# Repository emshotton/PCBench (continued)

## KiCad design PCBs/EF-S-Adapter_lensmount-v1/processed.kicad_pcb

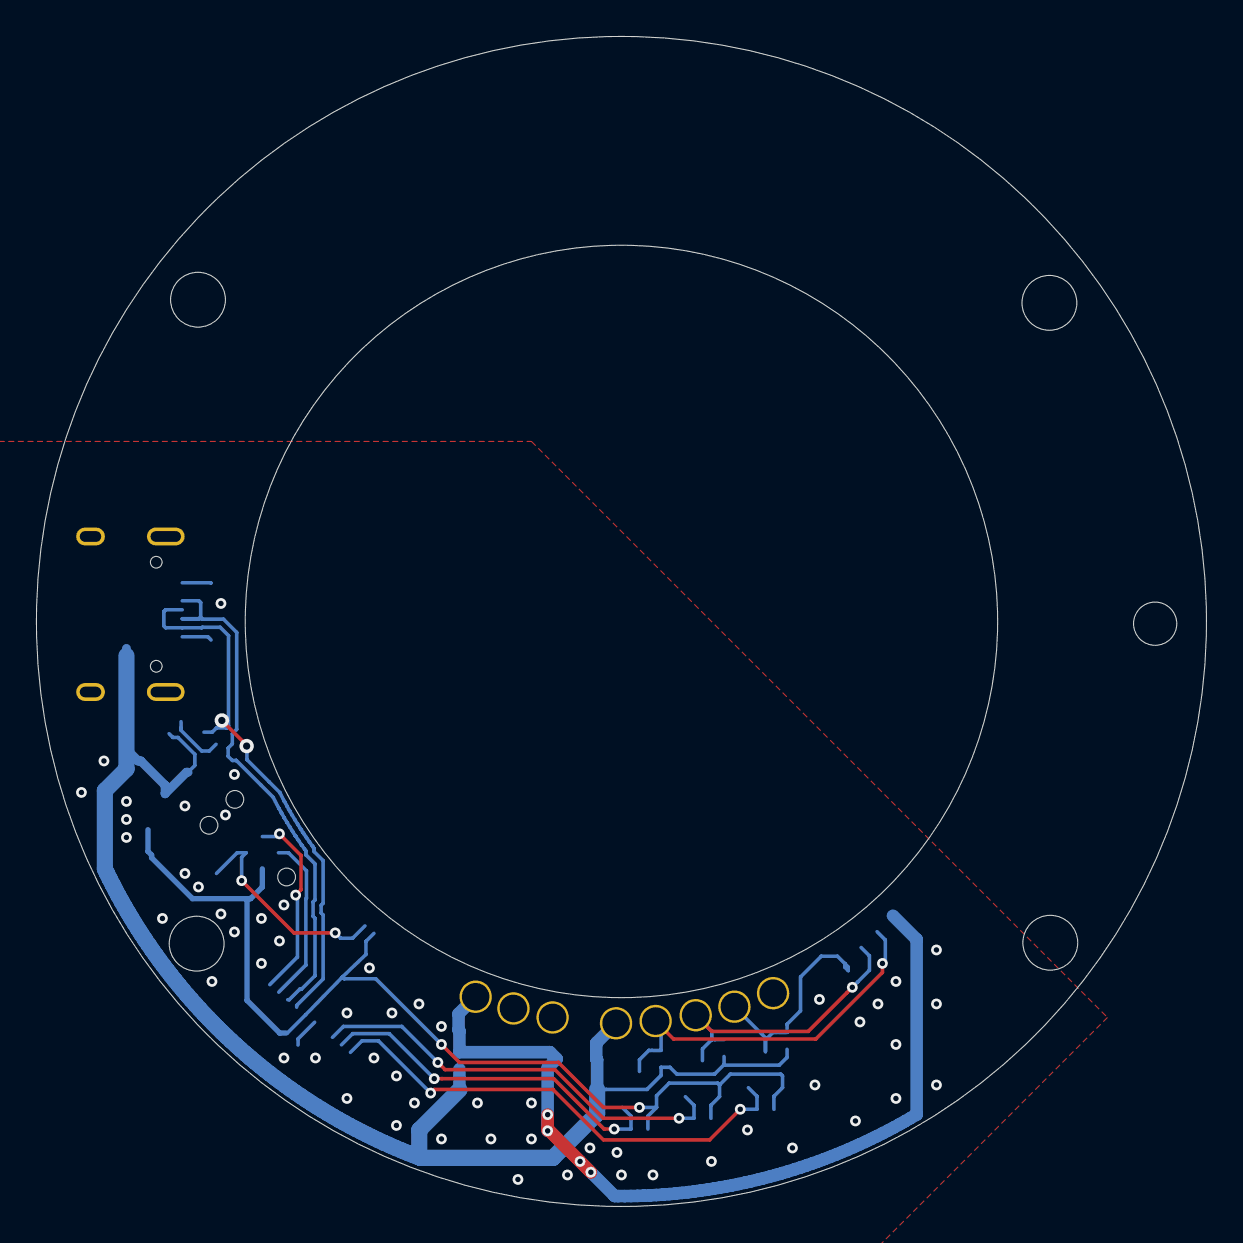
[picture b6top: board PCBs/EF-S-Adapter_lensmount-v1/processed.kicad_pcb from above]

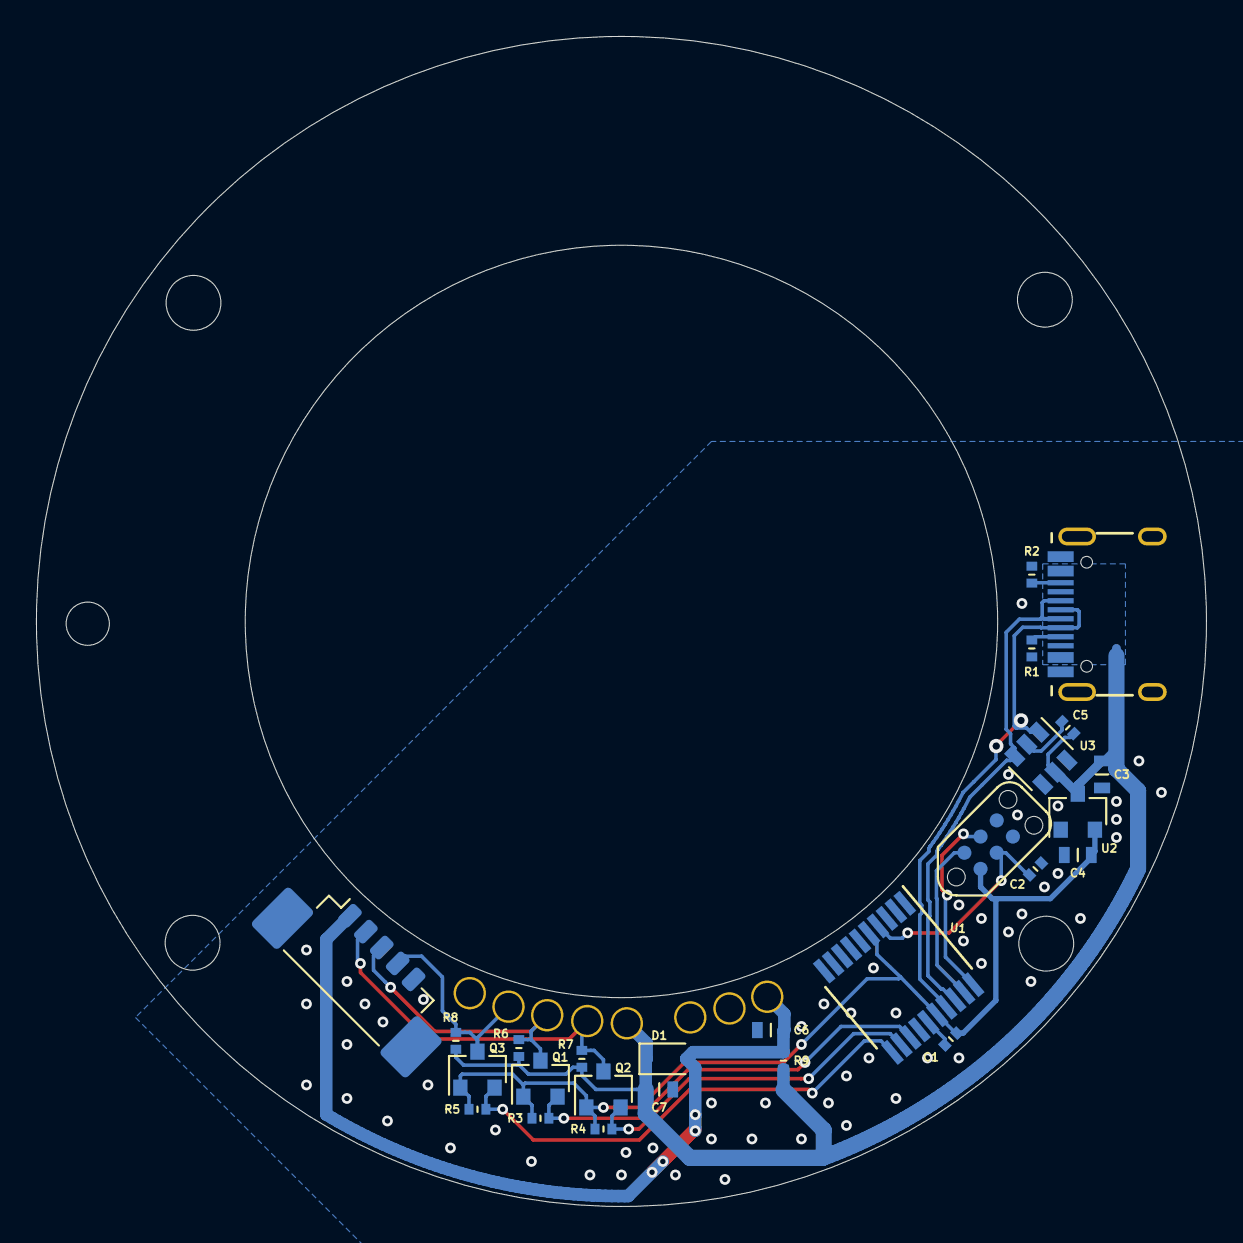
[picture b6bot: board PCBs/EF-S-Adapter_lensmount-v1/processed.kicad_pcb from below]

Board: 2 copper layers, 65.0 x 65.0 mm, 34 parts (26 on the bottom side), 17 nets.

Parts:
C1, C2, C5: 100n; C_0402
C3, C4, C6, C7: 1u; C_0603
D1: DNP; D_SOD-323F
J1: VBAT; PH-MVF-5365
J2, J3: AGND; PH-MVF-5365
J4: VDD; PH-MVF-5365
J5: DOUT; PH-MVF-5365
J6: DIN; PH-MVF-5365
J7: DCLK; PH-MVF-5365
J8: DGND; PH-MVF-5365
J9: USB; USB-C 16Pin
J10: Picoblade DNP; Molex_PicoBlade_53398-0571_1x05-1MP_P1.25mm_Vertical
P1: TC2030-CTX-Tag-Connect; TC2030
Q1, Q2, Q3: 2N7002; SOT-23
R1, R2, R3, R4, R5, R6, R7, R8, R9: 5k1; R_0402
U1: STM32F042F6Px; TSSOP-20_4.4x6.5mm_P0.65mm
U2: XC6206PxxxMR; SOT-23
U3: USBLC6-4; SOT-23-6

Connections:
+3V3: C1.1, C4.1, P1.1, Q1.1, Q2.1, Q3.1, R3.1, R4.1, R5.1, U1.5, U1.16, U2.2
+BATT: C6.1, D1.2, J1.1, J10.1, R9.1
D+: J9.A6, J9.B6, U1.18, U3.3
D-: J9.A7, J9.B7, U1.17, U3.1
DCLK_3V3: Q3.2, R5.2, U1.11
DCLK_5V: J7.1, J10.4, Q3.3, R8.2
DIN_3V3: Q1.2, R3.2, U1.13
DIN_5V: J6.1, J10.3, Q1.3, R6.2
DOUT_3V3: Q2.2, R4.2, U1.12
DOUT_5V: J5.1, J10.2, Q2.3, R7.2
GND: C1.2, C2.2, C3.2, C4.2, C5.2, C6.2, C7.2, J2.1, J3.1, J8.1, J9.A1, J9.A12, J9.B1, J9.B12, J9.S1, J10.5, J10.MP, P1.5, R1.1, R2.1, U1.15, U2.1, U3.2
NRST: C2.1, P1.3, U1.4
unnamed: J9.A5, R1.2
unnamed: J9.B5, R2.2
SWCLK: P1.4, U1.20
SWDIO: P1.2, U1.19
VBUS: C3.1, C5.1, C7.1, D1.1, J4.1, J9.A4, J9.A9, J9.B4, J9.B9, R6.1, R7.1, R8.1, R9.2, U2.3, U3.5

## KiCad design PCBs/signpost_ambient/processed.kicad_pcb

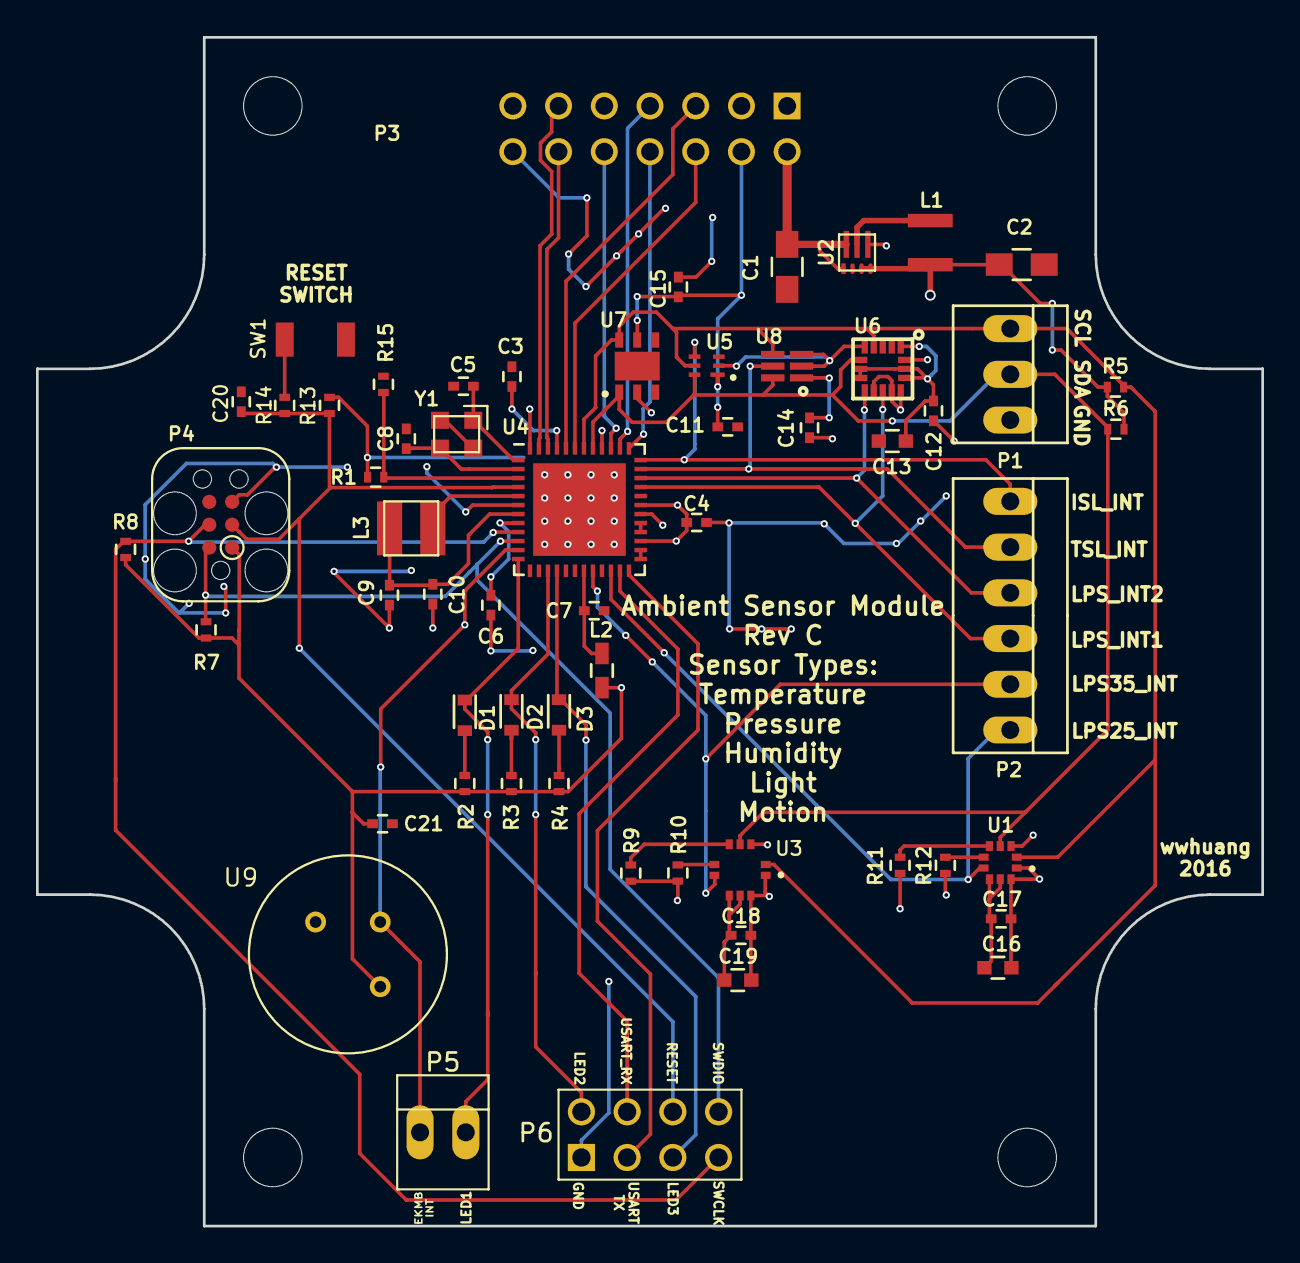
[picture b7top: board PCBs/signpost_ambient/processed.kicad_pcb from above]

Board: 4 copper layers, 68.1 x 66.0 mm, 63 parts (0 on the bottom side), 44 nets.

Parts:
C1, C2: GENERIC_C_0805; C_0805_HandSoldering
C3, C4, C6, C7, C10, C11, C12, C14, C15, C17, C18, C21: C_0.1u_0402_10V_10%_JB; C_0402
C5, C8, C20: GENERIC_C_0402; C_0402
C9: C_4.7u_0402_10V_10%_X5R; C_0402
C13, C16, C19: C_10u_0603_10V_10%_JB; C_0603
D1, D2, D3: LED; D_0603
H1, H2, H3, H4: SIGNPOST_HOLE
L1: .47 uH; DFE322512C
L2: 1.5k Ohm; C_0603_HandSoldering
L3: 22uH; 1212
P1: CONN_01X03; PINHEAD1-3
P2: CONN_01X06; PINHEAD1-6
P3: SIGNPOST_MODULE_GENERIC
P4: JLINK-TC; TC2030-IDC
P5: CONN_01X02; PINHEAD1-2
P6: CONN_02X04; PINHEAD2-4
R1, R5, R6: R_10k_0402_1%,100ppm/c,0.063W; R_0402
R2, R3, R4: R_1K_0402_1%,100ppm/c,0.2W; R_0402
R7, R8, R9, R10, R11, R12, R13: R_100K_0402_0.5%,25ppm/c,0.063W; R_0402
R14: GENERIC_R_0402; R_0402
R15: R_0_0402_.1W; R_0402
SW1: BSU-1000P; B3U-1000p
U1: LPS25HB; HLGA-10L_2.5x2.5mm
U2: TPS62086; RLT0007A
U3: LPS35HW; CCLGA-10L_3.5x3.5mm
U4: SAM4LC8A; QFN-48-1EP_7x7mm_Pitch0.5mm
U5: ISL29035; L6_1.5x1.6mm
U6: LPS331AP; HCLGA-16L
U7: Si7021; DFN_3x3mm_1mm
U8: TSL2561; DFN2
U9: EKMB1101111
Y1: FH1600015; FHXXX

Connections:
+3V3: C2.1, C3.1, C4.1, C6.1, C11.1, C12.1, C13.1, C14.1, C15.1, C16.1, C17.1, C18.1, C19.1, C21.1, L1.1, L2.2, P3.4, P4.1, R1.1, R2.2, R3.2, R4.2, R5.1, R6.1, R7.2, R8.1, R9.1, R10.1, R12.1, R13.1, U1.1, U1.10, U2.3, U2.4, U3.1, U3.10, U4.8, U4.27, U4.31, U4.40, U4.45, U5.1, U6.1, U6.7, U6.8, U6.14, U6.15, U7.5, U8.1, U9.2
+5V: C1.1, P3.2, U2.1, U2.7
/CNTR_PPS: P3.7, U4.38
/CNTR_SCL: P3.5, U4.44
/CNTR_SDA: P3.6, U4.43
/EKMB_INT: P5.1, U4.11, U9.1
/ISL_INT: P2.1, U4.36, U5.4
/LED_1: D1.1, P5.2, U4.12
/LED_2: D2.1, P6.2, U4.15
/LED_3: D3.1, P6.5, U4.16
/LPS25_INT: P2.6, U1.7, U4.22
/LPS35_INT: P2.5, U3.7, U4.20
/LPS_INT1: P2.4, U4.33, U6.11
/LPS_INT2: P2.3, U4.34, U6.9
/MOD_IN: P3.10, U4.39
/MOD_OUT: P3.8, U4.37
/SAM4L_RESET: C20.1, P4.3, P6.6, R13.2, R14.1, U4.4
/SAM4L_SWDCLK: P4.4, P6.7, R8.2, U4.9
/SAM4L_SWDIO: P4.2, P6.8, R7.1, U4.10
/TSL_INT: P2.2, U4.35, U8.5
/USART_RX: P6.4, U4.23
/USART_TX: P6.3, U4.24
/USB_D+: P3.11, U4.47
/USB_D-: P3.12, U4.46
/VDDANA: C7.1, L2.1, U4.19
/VDD_CORE: L3.1, U4.5
/VDD_OUT: C9.1, C10.1, L3.2, U4.7
/sensors/LPS25_CS: R12.2, U1.6
/sensors/LPS25_SA0: R11.2, U1.5
/sensors/LPS35_CS: R10.2, U3.6
/sensors/LPS35_SA0: R9.2, U3.5
/xin: C5.1, U4.1, Y1.1
/xout: C8.1, U4.2, Y1.3
GND: C1.2, C2.2, C3.2, C4.2, C5.2, C6.2, C7.2, C8.2, C9.2, C10.2, C11.2, C12.2, C13.2, C14.2, C15.2, C16.2, C17.2, C18.2, C19.2, C20.2, C21.2, P1.3, P3.1, P3.14, P4.5, P6.1, R11.1, R15.2, SW1.2, U1.3, U1.8, U1.9, U2.5, U3.3, U3.8, U3.9, U4.6, U4.17, U4.30, U4.48, U4.49, U5.2, U6.5, U6.10, U6.12, U6.13, U6.16, U7.2, U8.2, U8.3, U9.3, Y1.2, Y1.4
unnamed: D1.2, R2.1
unnamed: D2.2, R3.1
unnamed: D3.2, R4.1
unnamed: L1.2, U2.6
unnamed: R1.2, R15.1, U4.3
unnamed: R14.2, SW1.1
unnamed: U4.25, U4.26
unnamed: U4.28, U4.29
SCL: P1.1, R5.2, U1.2, U3.2, U4.42, U5.5, U6.4, U7.6, U8.4
SDA: P1.2, R6.2, U1.4, U3.4, U4.41, U5.6, U6.6, U7.1, U8.6

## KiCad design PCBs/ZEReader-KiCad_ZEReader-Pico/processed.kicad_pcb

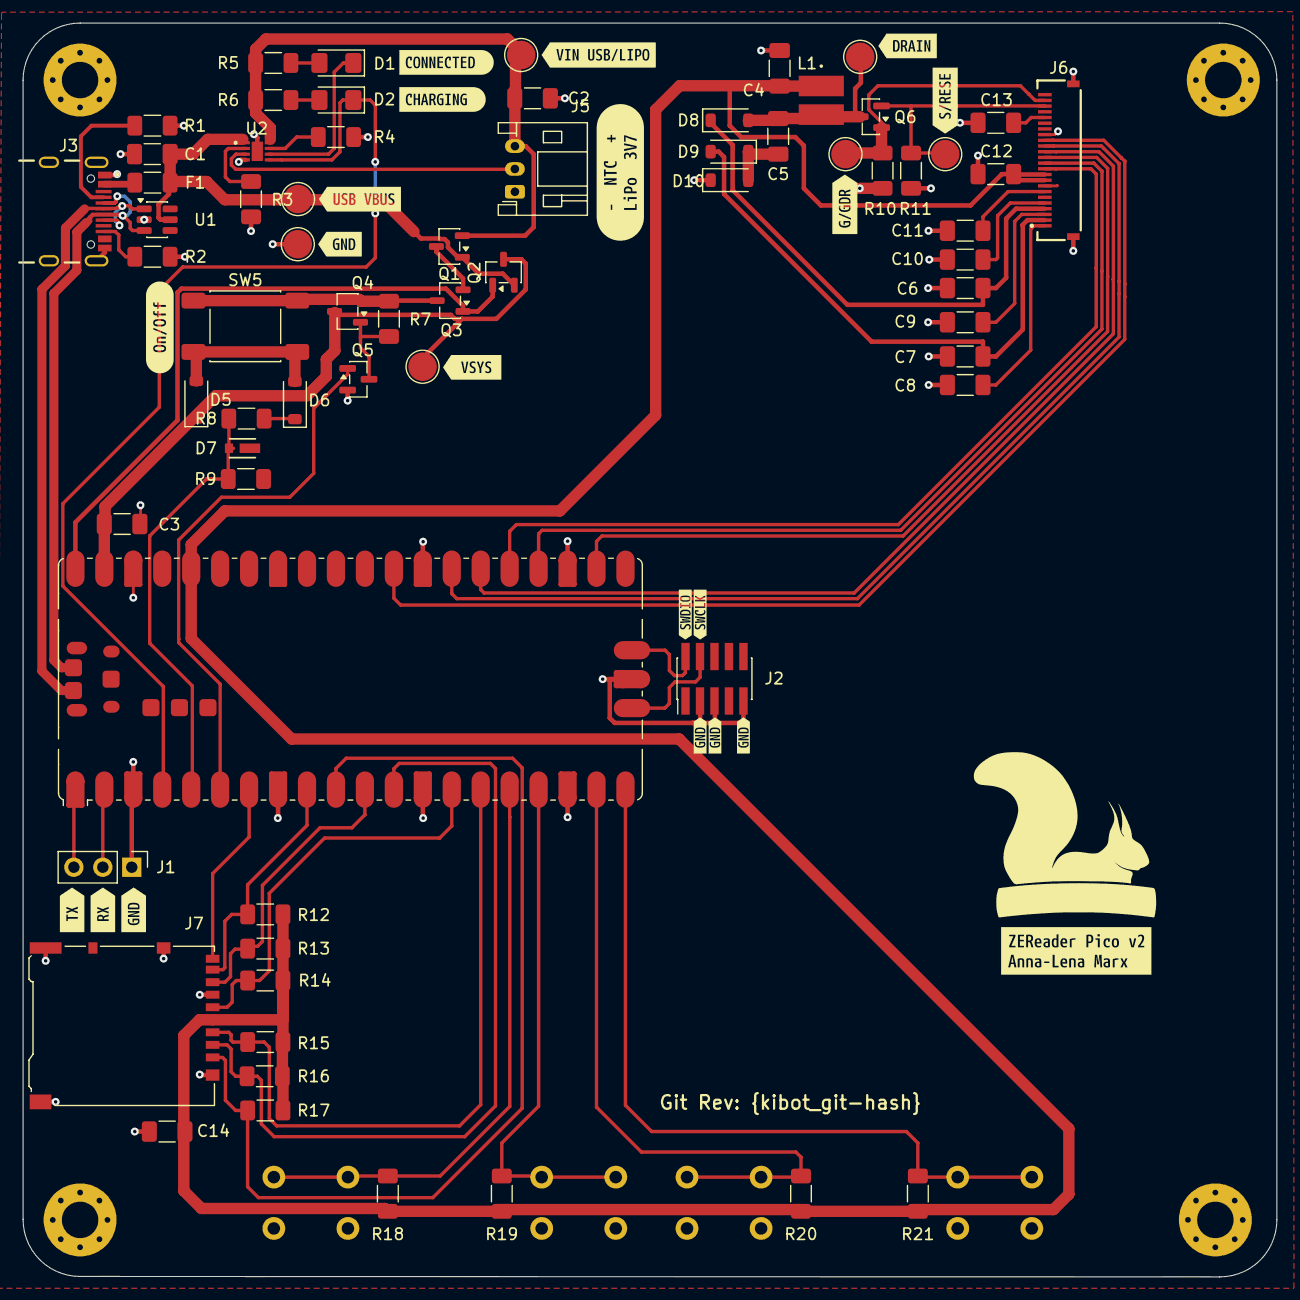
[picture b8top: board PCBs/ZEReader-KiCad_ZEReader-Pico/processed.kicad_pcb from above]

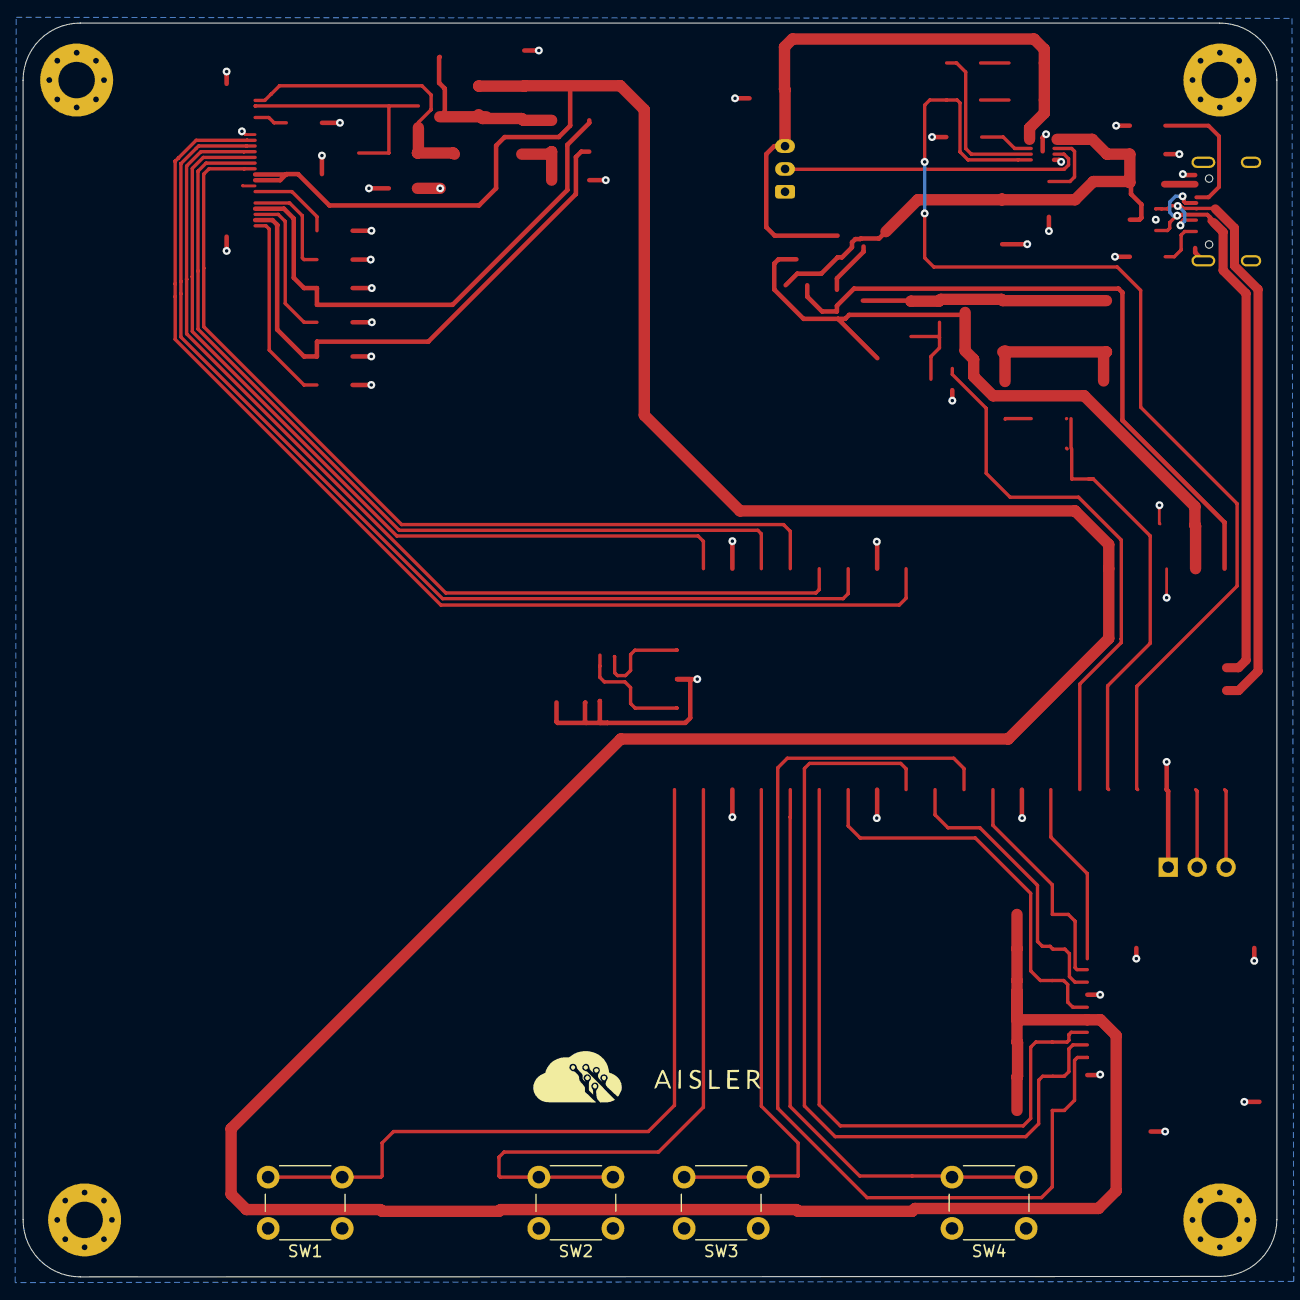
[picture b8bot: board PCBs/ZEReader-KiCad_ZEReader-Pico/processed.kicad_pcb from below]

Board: 2 copper layers, 110.0 x 110.0 mm, 96 parts (4 on the bottom side), 57 nets.

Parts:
A1: RaspberryPi_Pico; RaspberryPi_Pico_SMD
C1, C2, C3, C14: 10uF; C_1206_3216Metric_Pad1.33x1.80mm_HandSolder
C4, C5: 4.7uF; C_1206_3216Metric_Pad1.33x1.80mm_HandSolder
C6, C7, C9, C10, C13: 1uF, 25V; C_1206_3216Metric_Pad1.33x1.80mm_HandSolder
C8: 1uF, 50V; C_1206_3216Metric_Pad1.33x1.80mm_HandSolder
C11: 1uF, 10V; C_1206_3216Metric_Pad1.33x1.80mm_HandSolder
C12: 10uF, 10V; C_1206_3216Metric_Pad1.33x1.80mm_HandSolder
D1, D2: LED; LED_1206_3216Metric_Pad1.42x1.75mm_HandSolder
D5, D6, D8, D9, D10: MBR0530; D_SOD-123
D7: Zener 3V3; DIO_TDZVT_ROM
DRAIN1: BSS138_Drain; TestPoint_Pad_D2.5mm
F1: Polyfuse; R_1206_3216Metric_Pad1.30x1.75mm_HandSolder
G/GDR1: BSS138_Gate; TestPoint_Pad_D2.5mm
H1, H2, H3, H4: MountingHole_Pad; MountingHole_3.2mm_M3_Pad_Via
J1: UART; PinHeader_1x03_P2.54mm_Vertical
J2: Conn_02x05_Odd_Even; PinHeader_2x05_P1.27mm_Vertical_SMD
J3: USB4105-GF-A; GCT_USB4105-GF-A
J5: Conn_01x03_Socket; JST_PH_S3B-PH-K_1x03_P2.00mm_Horizontal
J6: FFC2B28-24-G; GCT_FFC2B28-24-G
J7: Micro_SD_Card_Det2; microSD_HC_Hirose_DM3AT-SF-PEJM5
L1: 10uH; IND_IFSC_1515AH_VIS-L
Q1, Q2, Q3, Q4: DMG2305UX-7; SOT-23-3
Q5, Q6: BSS138; SOT-23
R1, R2: 5.1k; R_1206_3216Metric_Pad1.30x1.75mm_HandSolder
R3: 604, 1%; R_1206_3216Metric_Pad1.30x1.75mm_HandSolder
R4: 27k, 1%; R_1206_3216Metric_Pad1.30x1.75mm_HandSolder
R5, R6, R7, R9, R10, R12, R13, R14, R15, R16, R17, R18, R19, R20, R21: 10k; R_1206_3216Metric_Pad1.30x1.75mm_HandSolder
R8: 1k; R_1206_3216Metric_Pad1.30x1.75mm_HandSolder
R11: 0.47; R_1206_3216Metric_Pad1.30x1.75mm_HandSolder
S/RESE1: BSS138_Source; TestPoint_Pad_D2.5mm
SW1, SW2, SW3, SW4: SW_Push; SW_PUSH_6mm
SW5: SW_Push; SW_Push_1P1T_NO_E-Switch_TL3301NxxxxxG
TP1: USB_VBUS; TestPoint_Pad_D2.5mm
TP2: V_USB_LIPO; TestPoint_Pad_D2.5mm
TP3: VSYS; TestPoint_Pad_D2.5mm
TP_GND1: TestPoint_Pad_D2.5mm
U1: USBLC6-2SC6; SOT-23-6
U2: BQ25170JDSGR; WSON8_BQ2517_TEX
kibuzzard-1: G***; kibuzzard-6910EAB5
kibuzzard-2: G***; kibuzzard-6910F1E0
kibuzzard-3: G***; kibuzzard-6910EA92
kibuzzard-4: G***; kibuzzard-6910F073
kibuzzard-5: G***; kibuzzard-6910F03B
kibuzzard-6: G***; kibuzzard-6910EACE
kibuzzard-7: G***; kibuzzard-6910EA89
kibuzzard-8: G***; kibuzzard-6910EAAC
kibuzzard-10: G***; kibuzzard-6910EB09
kibuzzard-14: G***; kibuzzard-6910EC15
kibuzzard-15: G***; kibuzzard-6910EC3B
kibuzzard-16: G***; kibuzzard-6910EC48
kibuzzard-17: G***; kibuzzard-6910ECBF
kibuzzard-691E57BD: G***; kibuzzard-691E57BD
kibuzzard-691E5833: G***; kibuzzard-691E5833
kibuzzard-691EE38D: G***; kibuzzard-691EE38D
kibuzzard-691EE385: G***; kibuzzard-691EE385
kibuzzard-691EE480: G***; kibuzzard-691EE480
kibuzzard-691EE489: G***; kibuzzard-691EE489
kibuzzard-691EE495: G***; kibuzzard-691EE495

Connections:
+3.3V: A1.36 (3V3), C4.1, C12.2, C14.1, J6.9, J6.10, J7.4 (VDD), L1.1, R12.1, R13.1, R14.1, R15.1, R16.1, R17.1, R18.2, R19.2, R20.1, R21.1
/01_MCU/BTN_1: A1.20 (GPIO15), R21.2, SW1.2
/01_MCU/BTN_2: A1.19 (GPIO14), R20.2, SW2.2
/01_MCU/BTN_3: A1.17 (GPIO13), R19.1, SW3.2
/01_MCU/BTN_4: A1.16 (GPIO12), R18.1, SW4.2
/01_MCU/CHARGING: A1.4 (GPIO2), D2.1 (K), U2.5 (STAT)
/01_MCU/EPD_BUSY: A1.29 (GPIO22), J6.16
/01_MCU/EPD_CS: A1.22 (GPIO17), J6.13
/01_MCU/EPD_DC: A1.26 (GPIO20), J6.14
/01_MCU/EPD_DIN: A1.25 (GPIO19), J6.11
/01_MCU/EPD_RST: A1.27 (GPIO21), J6.15
/01_MCU/EPD_SCK: A1.24 (GPIO18), J6.12
/01_MCU/SD_CLK-SCLK: A1.14 (GPIO10), J7.5 (CLK), R14.2
/01_MCU/SD_CMD-DI: A1.15 (GPIO11), J7.3 (CMD), R15.2
/01_MCU/SD_DAT0-DO: A1.11 (GPIO8), J7.7 (DAT0), R13.2
/01_MCU/SD_DAT1: A1.9 (GPIO6), J7.8 (DAT1), R12.2
/01_MCU/SD_DAT2: A1.10 (GPIO7), J7.1 (DAT2), R17.2
/01_MCU/SD_DAT3-CD-CS: A1.12 (GPIO9), J7.2 (DAT3/CD), R16.2
/01_MCU/SD_DET_B: A1.7 (GPIO5), J7.9 (DET_B)
/01_MCU/UC_OFF: A1.6 (GPIO4), Q5.1 (G)
/01_MCU/UC_ON_OFF_INTERRUPT: A1.5 (GPIO3), D7.1 (K), R8.1, R9.1
/01_MCU/USB_DN: A1.TP2 (USB_DM), J3.A7 (DN1), J3.B7 (DN2), U1.3 (I/O2)
/01_MCU/USB_DP: A1.TP3 (USB_DP), J3.A6 (DP1), J3.B6 (DP2), U1.1 (I/O1)
/01_MCU/VBUS: A1.40 (VBUS), Q2.1, Q3.1
/01_MCU/VSYS: A1.39 (VSYS), C3.1, D5.1 (K), Q2.3, Q4.3, TP3.1
/02a_USB-Battery-Charging/USB_VBUS: C1.1, F1.2, Q1.1, Q2.2, TP1.1, U1.5 (VBUS), U2.1 (IN)
/02a_USB-Battery-Charging/V_USB_LIPO: C2.1, J5.3, Q1.2, R5.2, R6.2, TP2.1, U2.8 (OUT)
/03_ePaper-Driver/Drain: C5.1, D8.2 (A), DRAIN1.1, L1.2, Q6.3 (D)
/03_ePaper-Driver/GDR: G/GDR1.1, J6.23, Q6.1 (G), R10.1
/03_ePaper-Driver/RESE: J6.22, Q6.2 (S), R11.2, S/RESE1.1
/03_ePaper-Driver/VGH: C6.1, D8.1 (K), J6.4
/03_ePaper-Driver/VGL: C7.1, D9.2 (A), J6.2
GND: A1.3 (GND), A1.8 (GND), A1.13 (GND), A1.18 (GND), A1.23 (GND), A1.28 (GND), A1.38 (GND), A1.D2 (GND), C1.2, C2.2, C3.2, C4.2, C6.2, C7.2, C8.1, C9.1, C10.1, C11.1, C12.1, C13.1, C14.2, D7.2 (A), D10.1 (K), H1.1, H2.1, H3.1, H4.1, J1.1, J2.3, J2.5, J2.9, J3.A1_B12 (GND), J3.B1_A12 (GND__1), J3.SH1 (SHELL_GND), J3.SH2 (SHELL_GND__1), J3.SH3 (SHELL_GND__2), J3.SH4 (SHELL_GND__3), J5.1, J6.8, J6.17, J6.S1 (SHIELD), J6.S2 (SHIELD__1), J7.6 (VSS), J7.10 (DET_A), J7.11 (SHIELD), Q5.2 (S), R1.1, R2.2, R3.2, R4.2, R9.2, R10.2, R11.1, SW1.1, SW2.1, SW3.1, SW4.1, TP_GND1.1, U1.2 (GND), U2.4 (GND), U2.9 (EPAD)
unnamed: A1.1 (GPIO0), J1.3
unnamed: A1.2 (GPIO1), J1.2
unnamed: A1.D1 (SWCLK), J2.4
unnamed: A1.D3 (SWDIO), J2.2
unnamed: C8.2, J6.1
unnamed: C9.2, J6.3
unnamed: C10.2, J6.5
unnamed: C11.2, J6.7
unnamed: C13.2, J6.20
unnamed: D1.2 (A), R5.1
unnamed: D1.1 (K), U2.6 (PG)
unnamed: D2.2 (A), R6.1
unnamed: D5.2 (A), D6.2 (A), SW5.2
unnamed: D6.1 (K), R8.2
unnamed: C5.2, D9.1 (K), D10.2 (A)
unnamed: J3.A5 (CC1), R1.2
unnamed: J3.B5 (CC2), R2.1
unnamed: F1.1, J3.A4_B9 (VBUS)
unnamed: J5.2, U2.3 (TS)
unnamed: Q1.3, Q3.2
unnamed: Q3.3, Q4.2, R7.1, SW5.1
unnamed: Q4.1, Q5.3 (D), R7.2
unnamed: R3.1, U2.2 (ISET)
unnamed: R4.1, U2.7 (VSET)
